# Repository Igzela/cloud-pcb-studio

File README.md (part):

> **Project priority and baseline.** The November 22 seven-board regression recorded **300 passing tests in 92.12 s**. Six boards had zero independent LVS opens, and Case 5 had one. The project roadmap prioritizes closing that gap and collecting the remaining evidence for engineering acceptance. [Roadmap](docs/project-roadmap.zh-CN.md) · [Handoff](docs/repository-handoff.zh-CN.md) · [Baseline report](docs/optimization-dense-escape-repair.zh-CN.md)

<div align="center">

# Cloud PCB Studio

**Headless Cloud Multi-Agent EDA Workbench & Board-Agnostic Blind PCB Solver**

*From JLCPCB BOM & SPICE physics to dual-pipeline autorouting, 4-layer planar magnetics, board-agnostic blind layout, and strict RS-274X / Excellon / Shapely LVS sign-off — 100% headless on Linux.*

> **中文概要** — **Cloud PCB Studio** 是一个全无头（Headless）云端多智能体 EDA 工程工作台与板级盲解（Blind）自动布局布线系统：覆盖 **器件选型/DFM 物理与 `ngspice-41` 仿真**、**双路布局布线（`@tscircuit/core` 与 KiCad/`fastroute` 竞速）**、**4 层同向磁通平面螺旋线圈与电容触摸专用 IP**、**零过拟合通用盲解引擎（在 3 块真实开源 PCB 上对比人工参考线长缩短 11.3%–47.5%）**，以及 **113/113 项严格零造假 VerifyGate 几何与拓扑 LVS 验收闭环**。

<br/>

*Independent Verification Workbench (`artifacts/verify/workbench.html`) — rendered & audited via headless Chromium (`1440×1080`, `0` console errors, `113 / 113` checks passed).*

</div>

## Current v3 solver and reproducible handoff

Use **Python 3.12** for the measured environment and load `source scripts/env.sh` before every Python, pytest or router invocation. A fresh clone needs its own virtual environment, Node dependencies, Playwright Chromium and ngspice. See [setup and current limitations](docs/repository-handoff.zh-CN.md). Runtime credentials and local dependency/cache directories are not distributed through Git.

Use the optimization workflow for new work. It preserves the frozen v3
artifacts and records each experiment in its own directory:

```bash
source scripts/env.sh
python -m scripts.optimize_pcb status
source scripts/env.sh
python -m scripts.optimize_pcb run --label my-change --variant dense-escape-repair --hypothesis "Describe the generic change and expected improvement"
source scripts/env.sh
python -m scripts.optimize_pcb history
```

Open `artifacts/blind_v3_caseN/assembly.html` directly in a browser; it contains
its own Three.js code and model geometry. Parametric package envelopes and
estimated heights are identified in `assembly_scene.json`; zero envelope
collisions alone does not certify unknown real mechanical dimensions.
See [the research and implementation limits](docs/v3-design-decisions.zh-CN.md).

The workflow runs pytest, all regression boards, strict audits and offline
browser checks before comparing each board against the baseline. A regression
on one board cannot be hidden by gains on another. An eligible experiment only
updates an artifact baseline pointer; it does not certify engineering quality.
Cases 1–5 and 10–11 are exposed regression data. Cases 6–9 and 12–13 remain
sealed for separate blind evaluations. [Optimization guide](docs/optimization-workflow.zh-CN.md)
The [first measured round](docs/optimization-first-round.zh-CN.md) records both
the connectivity improvement and the regression that prevented promotion.

The experimental `--variant supply-semantics` enables supply inference from
hierarchical voltage labels and typed power pins. It keeps evidence in
`effective_spec.json` and never invents missing current ratings. The default
solver remains on the stable behavior while the candidate is evaluated.

The `--variant scoped-supply` experiment distinguishes a single IC supply
domain, evidenced by typed supply pins, shunt return capacitors and passive
R/L/C endpoints, from board-level distribution. Unknown-current local domains
have an independent routing intent; backbone and explicit current/width
requirements retain priority. Scope and width provenance remain in the output.

For the user-selected independent Gemini reference, use
`scripts.run_gemini_reference` with model `gemini-4-hydrogen` and a runtime
credential. It sends anonymous blind input and records API provenance; it does
not treat a generated placement proposal as a routed or verified reference.
See [the external-reference protocol](docs/gemini-reference.zh-CN.md).

`scripts/run_blind_v3.py` is retained as the historical experiment entry point;
it writes the fixed v3 directories. Use `scripts.optimize_pcb` for daily work
so existing frozen results remain available for comparison.

---

## Why Cloud PCB Studio?

Most automated PCB demos stop at toy footprints or skip electrical, thermal, and manufacturing validation. **Cloud PCB Studio** treats PCB synthesis as a deterministic, physics-gated engineering pipeline where every stage emits typed contracts ([`contracts/schemas.py`](contracts/schemas.py)) and must survive independent geometric, electromagnetic, and circuit-level verification:

- **Physics Before Routing**: Rejects thermally fatal LDO traps (`197.2 °C` and `6212.8 °C` counterfactuals vs. `81.45 °C` synchronous buck), models trapezoidal copper etch + solder-mask dielectric loading (`-7.07 Ω` SE / `-15.33 Ω` Diff drop on `JLC04161H-7628`), checks MLCC DC-bias derating across all 18 capacitors, and verifies `ngspice-41` transient, Monte Carlo, and ESD clamp currents (`102.9×` reduction) before a trace is drawn.
- **Dual Synthesis + Real Autorouter Bake-Off**: Compiles Board 1 (`60 × 40 mm` USB-C PD Telemetry & Actuator Node) through both a code-first TSX pipeline (`@tscircuit/core` + `@tscircuit/capacity-autorouter`) and a programmatic KiCad/Specctra DSN/SES pipeline (`fastroute v0.1.14` vs. `freerouting-cli v2.5.0`).
- **Electromagnetic & Curved-Geometry Special IP**: Synthesizes Board 2 (`50 × 50 mm`) with a 4-layer stacked racetrack haptic coil whose alternating winding chirality (`+1, -1, +1, -1`) yields **`56.06×`** constructive axial flux (`45.209 µH` vs. `0.264 µH` canceling counterfactual), paired with a chevron CapTouch slider and `0.0 mm`-error serpentine meanders.
- **Board-Agnostic Blind Solver (`general_solver`)**: Consumes *only* an abstract `blind_spec.json` (never touching sealed human reference `.kicad_pcb` files) to place components, assign decoupling caps by capacitance & pin budget, insert pre-route SMD GND fanout vias, route via Specctra DSN/SES bake-off, pour 4-layer GND zones with stitching vias, and verify full 3D LVS/DRC.
- **Zero-Fake-Pass Gatekeeper (`verify_gate`)**: Strictly parses RS-274X Gerbers with `pygerber` (never patching malformed files on disk), Excellon drills exclusively with `gerbonara`, runs Shapely 3D topological LVS + via-in-pad checks, renders composite copper/mask/silk/drill PNGs via `resvg_py`, and audits the generated dashboard in headless Chromium.

---

## Architecture & 5-Stage EDA Pipeline

```mermaid
flowchart LR
    S1["1. Parts, DFM & SPICE\ncloud_pcb/parts_dfm\nJLCPCB BOM + JLC04161H-7628\nImpedance + ngspice-41"]
    S2["2. Dual Layout & Route\ncloud_pcb/layout_route\nPipeline A: tscircuit TSX\nPipeline B: KiCad + FastRoute"]
    S3["3. Special IP Geometry\ncloud_pcb/special_ip\n4L Stacked Planar Coil\nCapTouch + Meanders"]
    S4["4. Blind PCB Solver\ncloud_pcb/general_solver\nTopology Place + GND Fanout\n4L Pours + LVS Compare"]
    S5["5. VerifyGate & Workbench\ncloud_pcb/verify_gate\npygerber + gerbonara + Shapely\n113/113 Checks + Chromium UI"]

    C["contracts/schemas.py\nTyped Immutable Contracts"]

    S1 --> S2
    S2 --> S3
    S3 --> S4
    S4 --> S5
    S1 -.-> S5
    S2 -.-> S5
    S3 -.-> S5
    C -.-> S1
    C -.-> S2
    C -.-> S3
    C -.-> S4
    C -.-> S5
```

| Stage | Package / Entrypoint | Core Engine & Libraries | Key Verified Outputs |
| :--- | :--- | :--- | :--- |
| **1. Parts & DFM** | [`cloud_pcb/parts_dfm/`](cloud_pcb/parts_dfm/cli.py) | `PySpice`, `ngspice-41`, JLCPCB Basic/Preferred CSV + `jlcsearch` cache | [`artifacts/spec/`](artifacts/spec/dfm_budget.json) (`bom_verified.json`, `dfm_budget.json`, `spice_*.json`) |
| **2. Dual Layout & Route** | [`cloud_pcb/layout_route/`](cloud_pcb/layout_route/board1_kicad_fastroute.py) | `@tscircuit/core`, `esbuild`, `kiutils`, `fastroute v0.1.14`, `freerouting-cli v2.5.0`, `gerbonara`, `schemdraw` | [`artifacts/board1_tscircuit/`](artifacts/board1_tscircuit/tscircuit_report.json) & [`artifacts/board1_kicad_fastroute/`](artifacts/board1_kicad_fastroute/router_bakeoff.json) |
| **3. Special IP** | [`cloud_pcb/special_ip/`](cloud_pcb/special_ip/export_special_board.py) | Biot–Savart coil solver, Chaikin/arc fillets, serpentine meanders, `ngspice-41`, `pygerber` | [`artifacts/board2_special/`](artifacts/board2_special/board_manifest.json) (`special_board.kicad_pcb`, `coil_params.json`, Gerbers) |
| **4. General Blind Solver** | [`cloud_pcb/general_solver/`](cloud_pcb/general_solver/run_blind.py) | Netlist clustering, capacity-aware bypass matching, GND fanout vias, 4L pours, `compare_reference.py` | [`artifacts/blind_benchmark_v2/`](artifacts/blind_benchmark_v2/comparison_report.json), [`blind_case2/`](artifacts/blind_case2/comparison_report.json), [`blind_case3/`](artifacts/blind_case3/comparison_report.json) |
| **5. VerifyGate & UI** | [`cloud_pcb/verify_gate/`](cloud_pcb/verify_gate/__main__.py) & [`workbench_ui/`](cloud_pcb/workbench_ui/generate_workbench.py) | `pygerber`, `gerbonara`, `shapely`, `resvg_py`, headless Chromium | [`artifacts/verify/gate_report.json`](artifacts/verify/gate_report.json) & [`workbench.html`](artifacts/verify/workbench.html) |

---

## Visual Showcase

### Board 1 — USB-C PD Telemetry & Smart Actuator Node (`60 × 40 mm`, 4-Layer `JLC04161H-7628`)

Composite Gerber + Excellon renders generated by [`cloud_pcb/verify_gate/visual_inspect.py`](cloud_pcb/verify_gate/visual_inspect.py) using `pygerber`, `gerbonara`, and `resvg_py`:

| Pipeline B Top (`KiCad + FastRoute v0.1.14`) | Pipeline A Top (`@tscircuit/core`) | Pipeline B Bottom (`B_Cu + PTH/NPTH`) |
| :---: | :---: | :---: |
|  |  |  |
| `0` USB-path vias, `2.1 mm` VBUS trunk, `4` QFN thermal vias | `0` tscircuit errors, `64` vias, `440.46 mm` wirelength | `0` annular ring violations (`0.125 mm` min), `4` NPTH mounts |

### Board 2 — Special IP: 4-Layer Constructive Coil & Chevron CapTouch Slider (`50 × 50 mm`, 4-Layer)

| Top Layer (`F_Cu + F_Mask + F_SilkS + PTH`) | Inner Layer 1 (`In1_Cu` Counter-Wound Spiral) |
| :---: | :---: |
|  |  |
| 4 chevron electrodes (`0.3 mm` gap), GND guard ring, `0.0 mm`-error meanders, `SS33` flyback clamp | Polarity-inverted (`-1`) spiral maintaining CW current flow for `56.06×` axial flux addition |

### Blind Solver (`general_solver`) vs. Human Reference — 3 Real Open-Source Boards

Each comparison below pits the **board-agnostic blind solver** (left, consuming only `blind_spec.json`) against the **original human-designed open-source KiCad PCB** (right):

#### Case 1: STM32 CAN + IMU Sensor Board (`can_sensor_board_hw`, `55.0 × 45.0 mm`, 36 nets)

#### Case 2: ESP32-WROOM-32E Flight Controller (`esp32_flight_controller_rev2`, `67.5 × 53.5 mm`, 50 nets)

#### Case 3: Dual MCT8314ZH BLDC Motor Driver (`sima_bldc_motor_driver`, `50.0 × 50.0 mm`, 56 nets)

---

## Verified Quantitative Results

All numbers below are extracted directly from the checked-in verification artifacts on disk (`artifacts/verify/gate_report.json`, `artifacts/spec/*.json`, `artifacts/board1_kicad_fastroute/router_bakeoff.json`, `artifacts/board2_special/*.json`, and `artifacts/blind_*/comparison_report.json`).

### VerifyGate (`113 / 113` Checks Passed · `0` Critical / `0` High)

| Audit Suite | Checks Passed | Critical / High | Verified Highlights |
| :--- | :---: | :---: | :--- |
| **`board1_spec`** | `14 / 14` | `0 / 0` | `JLC04161H-7628` masked impedance **`50.08 Ω`** SE / **`89.64 Ω`** Diff; `47` BOM placements (`0` low-stock parts); Buck `Tj = 81.45 °C`, LDO `Tj = 49.93 °C`; `ngspice-41` transient, MC (`1593.79 Hz`), ESD clamp (`1.603 mA`) |
| **`board1_pipeline_b`** | `40 / 40` | `0 / 0` | `pygerber` & `gerbonara` clean RS-274X/Excellon; `0` LVS opens/shorts; `0` via-in-pad collisions; `0.1517 mm` min inter-net clearance; `0.0 mm²` silk-to-mask overlap; `0` USB path vias; `2.1 mm` VBUS width; `4` QFN thermal vias |
| **`board1_pipeline_a`** | `30 / 30` | `0 / 0` | `0` tscircuit errors; `2.4331 mm` USB-C-to-TVS stub; `0` USB path vias; `2.1 mm` VBUS width; distinct CC1/CC2 nets; `0` LVS opens/shorts; `0.1007 mm` min clearance; `0.125 mm` min annular ring |
| **`board2_special`** | `29 / 29` | `0 / 0` | **`56.06×`** constructive coil flux (`4042.89` vs `72.12 µT/A`); `45.209 µH` vs `0.264 µH`; **`0.33%`** SPICE $\tau$ error; `3.5985 V` Schottky clamp; `0` LVS shorts; `0.5065 mm` min clearance; `2.65 mm` copper-to-edge margin |
| **Headless Chromium** | `PASS` | `0` errors | `workbench.html` (`1,045,708` DOM chars), `1440×1080` screenshot (`pixel_std = 63.96`), all 5 PyGerber composite renders verified non-blank |
| **Total** | **`113 / 113`** | **`0 / 0`** | **`overall_passed = true` · `defect_tickets = []`** |

<details>
<summary><strong>Stage 1 Physics, JLCPCB BOM & ngspice-41 Verification Metrics</strong></summary>

| Domain | Metric | Measured Result | Engineering Target / Notes |
| :--- | :--- | :--- | :--- |
| **Stackup & Impedance** | `JLC04161H-7628` 4L (`ENIG`) SE `50 Ω` | **`50.08 Ω`** masked (`57.15 Ω` bare) | `12.06 mil` drawn (`11.665 mil` trapezoid eff.); `-7.07 Ω` mask drop |
| **Stackup & Impedance** | `JLC04161H-7628` 4L (`ENIG`) Diff `90 Ω` | **`89.64 Ω`** masked (`104.96 Ω` bare) | `8.31 mil` W / `5.0 mil` S (`-15.33 Ω` mask drop) |
| **JLCPCB BOM (Qty 5)** | PCBA cost per board | **`$13.63 / bd`** (`$13.6317/bd`) | `$68.16` total PCBA (`$7.824/bd` components), `47` placements (`27` unique, `181` joints) |
| **JLCPCB Supply Chain** | Basic / Preferred & stock health | **`87.2%`** Basic/Preferred · **`100%` stock > 100** | `17` Basic + `4` Preferred + `6` Extended; lowest stock = `408` (`STM32G0B1CEU6`); dual `5.1 kΩ` (`R1`, `R2`) |
| **Thermal Crossover** | Buck `3.3 V @ 1.2 A` vs. LDO traps | **`81.45 °C` PASS** (`TPS54202HDDCR`) | LDO `20V->3.3V @ 1.2A` (`6212.8 °C`) & `5V->3.3V @ 0.3A` (`197.2 °C`) rejected; `2.5V` LDO `49.93 °C` PASS |
| **ngspice-41 Power** | `20 V -> 3.3 V` Buck + `2.5 V` LDO | **`3.2981 V`** (`18.054 mVpp`) / **`2.4984 V`** (`0.0062 mVpp`) | `0.4 -> 1.2 A` step: `172.77 mV` Buck undershoot, `0.1026 mV` LDO max deviation |
| **ngspice-41 Monte Carlo** | 30-run RC filter (`1 kΩ ±1%`, `100 nF ±10%`) | **`1593.79 Hz`** mean (`0.0014%` nominal err) | `0` imaginary-frequency anomalies; capacitor accounts for `99.5%` of $f_c$ variance |
| **ngspice-41 ESD Clamp** | `USBLC6-2SC6` + `1 kΩ` limiter vs. `1 Ω` | **`164.91 mA -> 1.603 mA`** (**`102.9×`** reduction) | Peak IC pin voltage clamped `5.354 V -> 3.916 V`; well below `20 mA` latchup threshold |
| **Board 2 EM & SPICE** | 4L stacked coil (`51` turns, `2732.8 mm`) | **`56.06×` flux** · **`45.209 vs 0.264 µH`** · **`0.33%` $\tau$ err** | `4042.89` vs `72.12 µT/A`; $\tau_{\text{sim}} = 7.6558\,\mu\text{s}$ vs $7.681\,\mu\text{s}$; `SS33` clamped `3.5985 V` |

</details>

### 3-Way Autorouter Bake-Off (Board 1)

| Autorouter Engine | Status | Routed Nets | Unrouted | Vias | Wirelength | Runtime | Engineering Notes |
| :--- | :---: | :---: | :---: | :---: | :---: | :---: | :--- |
| **`fastroute v0.1.14`** *(Winner)* | **PASS** | **`23 / 23`** | **`0`** | `16` *(route SES)* | `564.99 mm` | `10,351.5 ms` | `0` violations, `0` USB path vias; selected for final Pipeline B Gerbers (`20` KiCad vias incl. 4 QFN thermal) |
| **`freerouting-cli v2.5.0`** | **FAIL** | `22 / 23` | `6` | `12` | `507.01 mm` | `3,951.9 ms` | `0` USB path vias; capped at `max_passes=1` (v2.5.0 GraalVM `BoardSnapshotManager` crashes when `max_passes > 1`) |
| **`tscircuit_capacity_autorouter`** | **PASS** | **`24 / 24`** | **`0`** | `64` | **`440.46 mm`** | *(Node bundle)* | `0` errors, `0` USB path vias; powers code-first Pipeline A (`board1.tsx`) |

### Board-Agnostic Blind Solver (`general_solver`) vs. Human Reference

Evaluated strictly zero-overfitting (`blind_spec.json` only) against three real open-source KiCad projects:

| Benchmark Board | Size & Nets | Wirelength (Blind vs. Human) | Length Delta | Routed Nets | Vias (Blind vs. Human) | LVS Opens / Shorts (Blind) | Key Highlights & Honest Audit Notes |
| :--- | :---: | :---: | :---: | :---: | :---: | :---: | :--- |
| **Case 1: [`can_sensor_board_hw`](https://github.com/HardyYu/can_sensor_board_hw)** | `55.0 × 45.0 mm` · `36` nets | **`963.6 mm`** vs. `1086.9 mm` | **`-11.3%`** | **`36 / 36`** | `86` (`34` Sig / `52` GND) vs. `118` (`41` / `77`) | **`0 / 0`** | `CAN_H`/`CAN_L` mismatch `3.012 mm` vs. `8.684 mm` (Human); `86.8%` 4L GND pour; `0.1317 mm` min clearance |
| **Case 2: [`esp32_flight_controller_rev2`](https://github.com/shazmeenShz/ESP32-Flight-Controller)** | `67.5 × 53.5 mm` · `50` nets | **`1261.5 mm`** vs. `2400.6 mm` | **`-47.5%`** | **`50 / 50`** | `127` (`56` Sig / `71` GND) vs. `45` (`41` / `4`) | **`0 / 0`** | Both USB diff pairs matched to **`0.100 mm`** skew (vs. `33.79 mm` / `1.07 mm` Human); `91.75%` 4L GND pour; `4.82 mm` avg header edge dist (vs. `18.19 mm`) |
| **Case 3: [`sima_bldc_motor_driver`](https://github.com/lio-tam/Autonomous-SIMA-Robot)** | `50.0 × 50.0 mm` · `56` nets | **`1171.6 mm`** vs. `1506.2 mm` | **`-22.2%`** | **`55 / 56`** | `149` (`79` Sig / `70` GND) vs. `134` (`98` / `36`) | **`1 / 0`** | **1 unrouted LVS open** on `/M2_BRAKE` (2 islands, 3 pads); **`0` shorts** (`0.1317 mm` min clr). *(Note: unedited Human Ref exhibits `12` `F.Cu` LVS shorts / `0.0 mm` min clr)* |

---

## Quick Setup & Reproducible Runs

### 1. Provision Cloud EDA Toolchain (`scripts/setup_cloud_eda.sh`)

[`scripts/setup_cloud_eda.sh`](scripts/setup_cloud_eda.sh) bootstraps the entire headless toolchain in user space (`.venv`, `.mamba/ngspice`, `node_modules`, `bin/{fastroute,freerouting-cli}`, and `data/` JLCPCB caches):

```bash
bash scripts/setup_cloud_eda.sh
source scripts/env.sh
```

> **Note**: Sourcing [`scripts/env.sh`](scripts/env.sh) puts `.venv/bin`, `bin/`, `.mamba/ngspice/bin`, and `node_modules/.bin` onto `PATH` while keeping tool caches inside `.run/`. Pre-built Linux x64 binaries for `fastroute` (`v0.1.14`) and `freerouting-cli` (`v2.5.0`) are already included under [`bin/`](bin/).

### 2. Run Individual Pipelines & Blind Benchmarks

```bash
source scripts/env.sh

# Stage 1: JLCPCB BOM selection, DFM stackup/impedance, and ngspice-41 power/ESD/MC sims
python -m cloud_pcb.parts_dfm --qty 5 --mc-runs 30

# Stage 2A & 2B: Board 1 code-first tscircuit + KiCad/FastRoute 3-way bake-off
python -m cloud_pcb.layout_route.board1_tscircuit
python -m cloud_pcb.layout_route.board1_kicad_fastroute

# Stage 3: Board 2 Special IP (4L stacked coil, chevron CapTouch, meanders, ngspice)
python -m cloud_pcb.special_ip.export_special_board --out artifacts/board2_special

# Stage 4: Board-agnostic blind solver + quantitative side-by-side comparison (Case 1 / 2 / 3)
python -m cloud_pcb.general_solver.run_blind \
  --spec benchmark_case/blind_spec.json \
  --outdir artifacts/blind_benchmark_v2

python -m cloud_pcb.general_solver.compare_reference \
  --blind artifacts/blind_benchmark_v2/routed.kicad_pcb \
  --ref benchmark_case/sealed_reference/can_sensor_board_kicad/Sensor_Board.kicad_pcb \
  --spec benchmark_case/blind_spec.json \
  --out-json artifacts/blind_benchmark_v2/comparison_report.json \
  --out-png artifacts/blind_benchmark_v2/comparison_side_by_side.png

# Case 2 (ESP32 Flight Controller) & Case 3 (Dual BLDC Driver)
python -m cloud_pcb.general_solver.run_blind \
  --spec benchmark_case/blind_spec_case2.json \
  --outdir artifacts/blind_case2

python -m cloud_pcb.general_solver.run_blind \
  --spec benchmark_case/blind_spec_case3.json \
  --outdir artifacts/blind_case3

# Stage 5: Independent Zero-Fake-Pass VerifyGate (strict mode exits non-zero on CRITICAL/HIGH tickets)
python -m cloud_pcb.verify_gate --strict
```

### 3. Run the Test Suite (`26` Unit & Integration Tests)

```bash
source scripts/env.sh
python -m pytest -v
```

<details>
<summary><strong>Zero-Fake-Pass Verification Policy & Negative Tests</strong></summary>

[`tests/test_verify_gate.py`](tests/test_verify_gate.py) includes adversarial fault-injection tests confirming that [`cloud_pcb/verify_gate`](cloud_pcb/verify_gate/gerber_drc.py) refuses to silently pass broken outputs:
- Rejects malformed RS-274X syntax (`G75` missing `*` terminator) via strict `pygerber` parsing.
- Rejects low-stock BOM parts (`stock <= 100`), negative/non-finite Monte Carlo corner frequencies (`-1.8e199` / `NaN`), and ESD pin clamp currents `>= 20 mA`.
- Rejects Board 2 coil $\tau$ step errors `>= 2.0%` or constructive flux ratios `<= 10×`.
- Isolates Excellon drill parsing strictly to `gerbonara.excellon.ExcellonFile` and verifies copper-to-edge margins, annular rings, via-in-non-thermal-SMT-pad collisions, and multi-layer LVS connectivity.

</details>

---

## Repository Structure

```text
cloud-pcb-studio/
├── bin/                        # Pre-built fastroute (v0.1.14) & freerouting-cli (v2.5.0) binaries
├── contracts/
│   └── schemas.py              # Typed dataclasses (StackupProfile, SelectedPart, GateReport, VerifyTicket)
├── cloud_pcb/
│   ├── parts_dfm/              # Stage 1: JLCPCB catalog, DFM physics, ngspice-41 simulations
│   ├── layout_route/           # Stage 2: board1.tsx (tscircuit) & board1_kicad_fastroute.py (DSN/SES)
│   ├── special_ip/             # Stage 3: 4L planar coil, chevron CapTouch, Chaikin & meander routing
│   ├── general_solver/         # Stage 4: board-agnostic blind solver & reference comparison tool
│   ├── verify_gate/            # Stage 5: pygerber/gerbonara/Shapely LVS/DRC & Chromium visual inspector
│   └── workbench_ui/           # Standalone interactive HTML verification dashboard generator
├── benchmark_case/             # Blind specs (Cases 1–3) & sealed open-source KiCad human references
├── artifacts/                  # Generated specs, KiCad PCBs, Gerbers, renders, workbench & comparison PNGs
├── data/                       # Cached JLCPCB Basic/Preferred CSV & jlcsearch snapshots
├── scripts/                    # setup_cloud_eda.sh & env.sh headless environment wrappers
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
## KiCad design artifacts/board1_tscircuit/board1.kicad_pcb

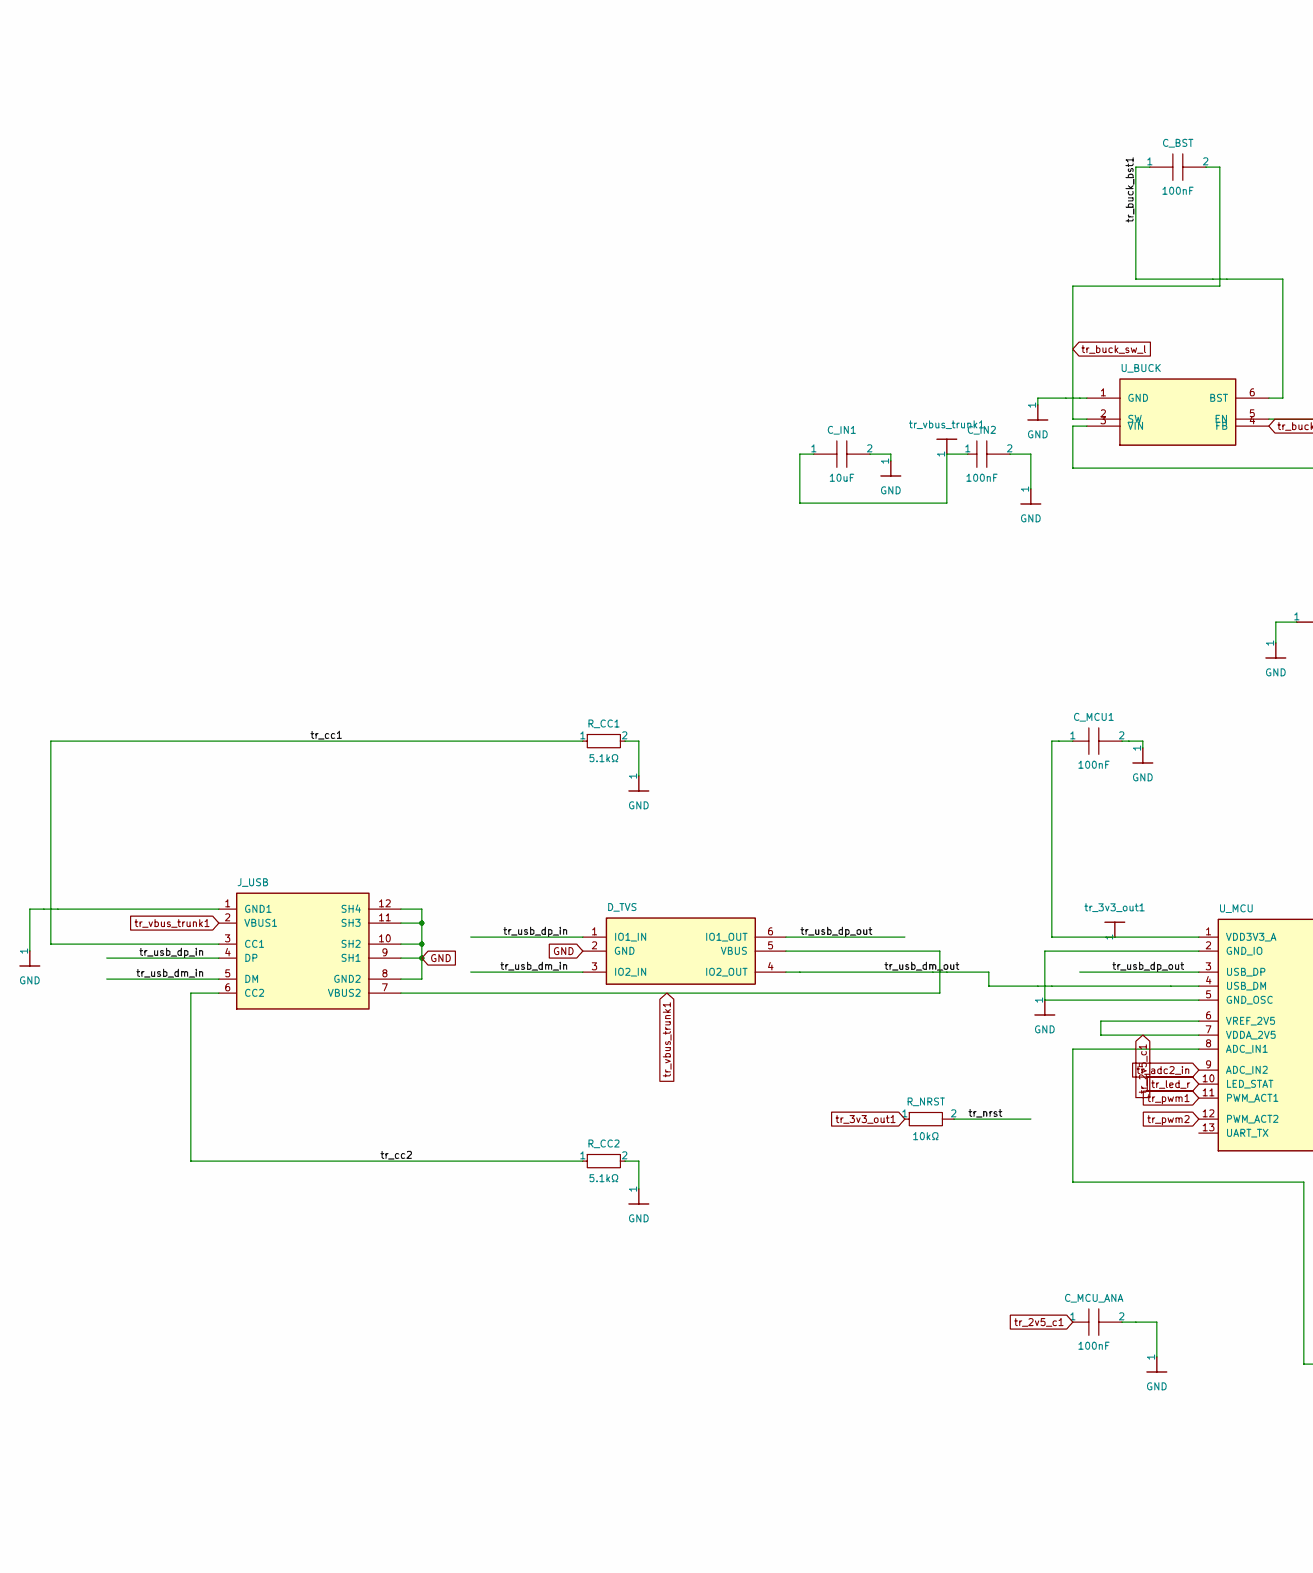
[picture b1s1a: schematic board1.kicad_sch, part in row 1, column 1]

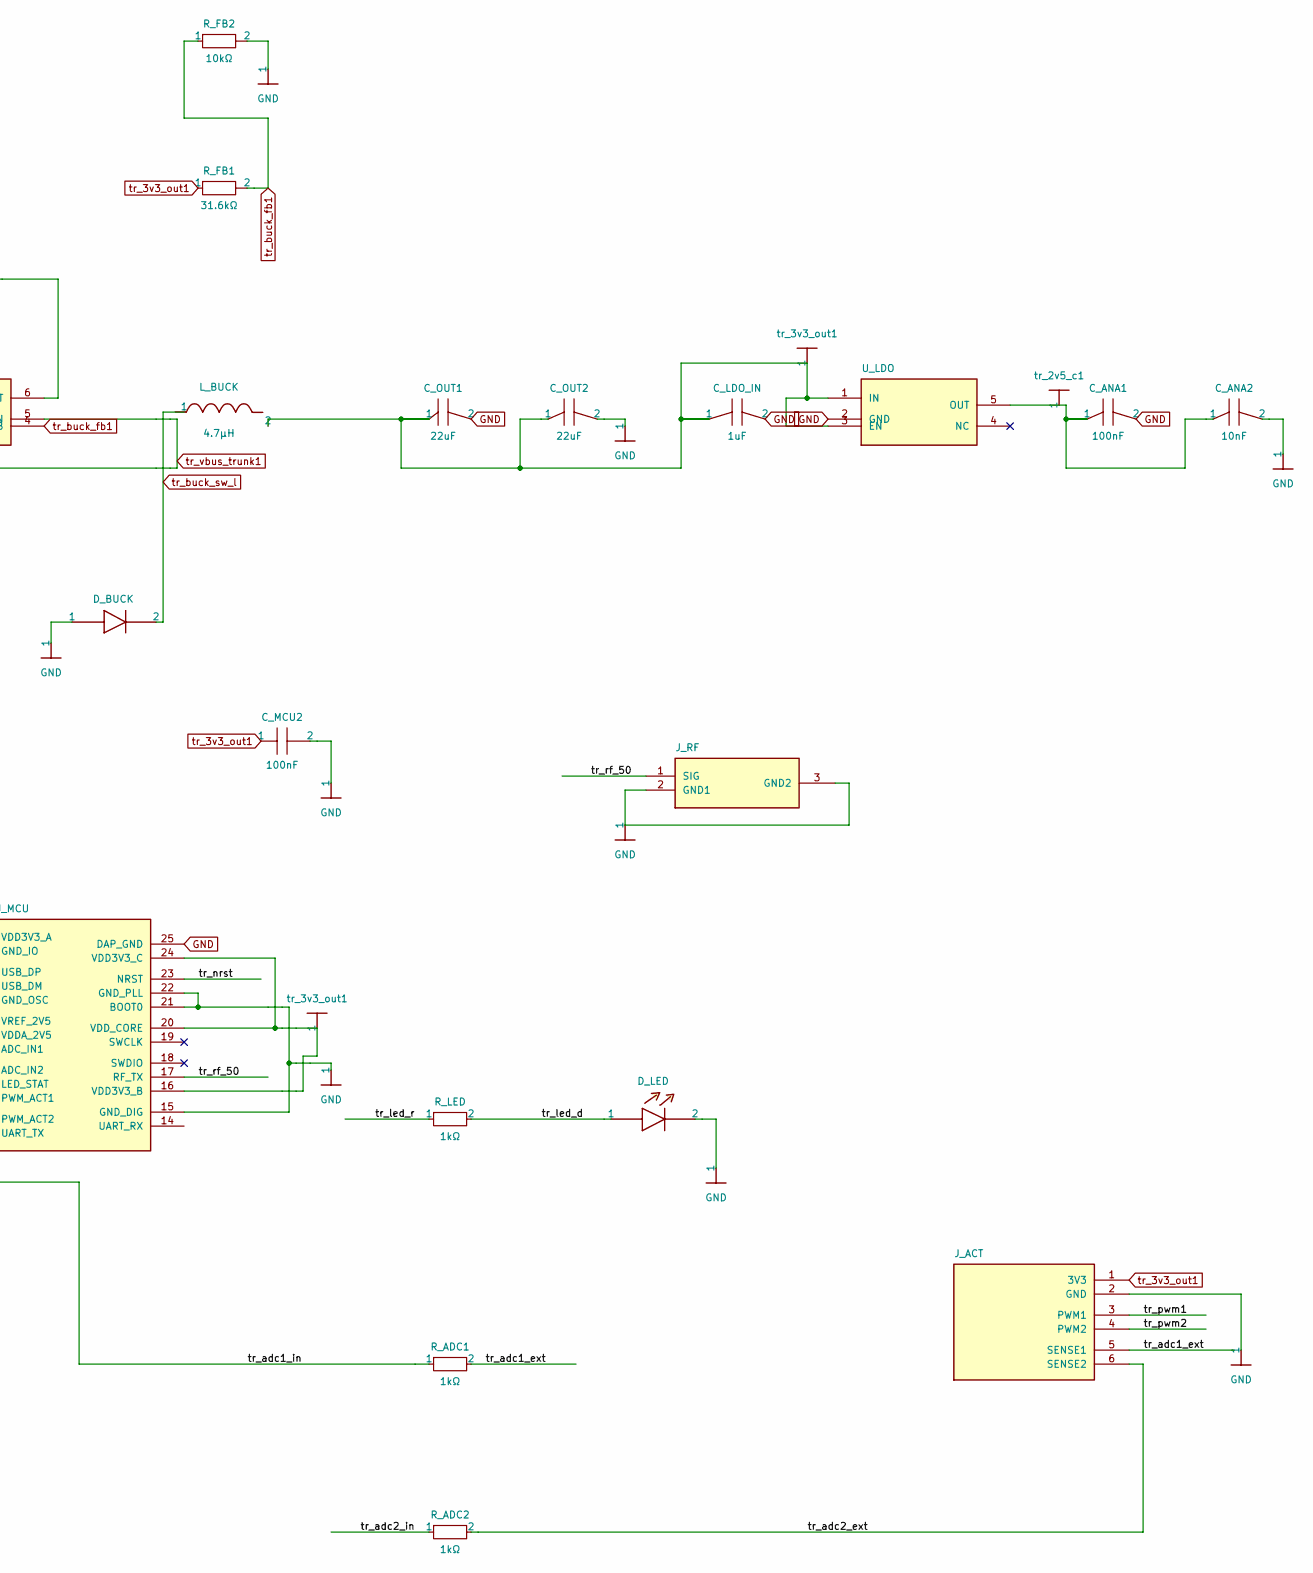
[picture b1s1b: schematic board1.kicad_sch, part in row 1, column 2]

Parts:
C_ANA1: 100nF
C_ANA2: 10nF
C_BST: 100nF
C_IN1: 10uF
C_IN2: 100nF
C_LDO_IN: 1uF
C_MCU1, C_MCU2: 100nF
C_MCU_ANA: 100nF
C_OUT1, C_OUT2: 22uF
D_BUCK: (no value)
D_LED: (no value)
D_TVS: (no value)
J_ACT: J_ACT
J_RF: (no value)
J_USB: (no value)
L_BUCK: 4.7µH
R_ADC1, R_ADC2: 1kΩ
R_CC1, R_CC2: 5.1kΩ
R_FB1: 31.6kΩ
R_FB2: 10kΩ
R_LED: 1kΩ
R_NRST: 10kΩ
U_BUCK: (no value)
U_LDO: (no value)
U_MCU: (no value)

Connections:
.D_TVS > .IO1_OUT to .U_MCU > .USB_DP: D_TVS.6 (IO1_OUT), U_MCU.3 (USB_DP)
.D_TVS > .IO2_OUT to .U_MCU > .USB_DM: D_TVS.4 (IO2_OUT), U_MCU.4 (USB_DM)
.J_USB > .CC1 to .R_CC1 > .pin1: J_USB.3 (CC1), R_CC1.1
.J_USB > .CC2 to .R_CC2 > .pin1: J_USB.6 (CC2), R_CC2.1
.J_USB > .DM to .D_TVS > .IO2_IN: D_TVS.3 (IO2_IN), J_USB.5 (DM)
.J_USB > .DP to .D_TVS > .IO1_IN: D_TVS.1 (IO1_IN), J_USB.4 (DP)
.J_USB > .VBUS1 to .C_IN1 > .pin1: C_IN1.1, C_IN2.1, D_TVS.5 (VBUS), J_USB.2 (VBUS1), J_USB.7 (VBUS2), U_BUCK.3 (VIN), U_BUCK.5 (EN)
.R_ADC1 > .pin2 to .J_ACT > .pin5: J_ACT.5 (SENSE1), R_ADC1.2
.R_ADC2 > .pin2 to .J_ACT > .pin6: J_ACT.6 (SENSE2), R_ADC2.2
.R_FB1 > .pin1 to .C_OUT1 > .pin1: C_LDO_IN.1, C_MCU1.1, C_MCU2.1, C_OUT1.1, C_OUT2.1, J_ACT.1 (3V3), L_BUCK.2, R_FB1.1, R_NRST.1, U_LDO.1 (IN), U_LDO.3 (EN), U_MCU.1 (VDD3V3_A), U_MCU.16 (VDD3V3_B), U_MCU.20 (VDD_CORE), U_MCU.24 (VDD3V3_C)
.R_LED > .pin2 to .D_LED > .anode: D_LED.1, R_LED.2
.R_NRST > .pin2 to .U_MCU > .NRST: R_NRST.2, U_MCU.23 (NRST)
.U_BUCK > .BST to .C_BST > .pin1: C_BST.1, U_BUCK.6 (BST)
.U_BUCK > .FB to .R_FB1 > .pin2: R_FB1.2, R_FB2.1, U_BUCK.4 (FB)
.U_BUCK > .SW to .L_BUCK > .pin1: C_BST.2, D_BUCK.2, L_BUCK.1, U_BUCK.2 (SW)
.U_LDO > .OUT to .C_ANA1 > .pin1: C_ANA1.1, C_ANA2.1, C_MCU_ANA.1, U_LDO.5 (OUT), U_MCU.6 (VREF_2V5), U_MCU.7 (VDDA_2V5)
.U_MCU > .ADC_IN1 to .R_ADC1 > .pin1: R_ADC1.1, U_MCU.8 (ADC_IN1)
.U_MCU > .ADC_IN2 to .R_ADC2 > .pin1: R_ADC2.1, U_MCU.9 (ADC_IN2)
.U_MCU > .LED_STAT to .R_LED > .pin1: R_LED.1, U_MCU.10 (LED_STAT)
.U_MCU > .PWM_ACT1 to .J_ACT > .pin3: J_ACT.3 (PWM1), U_MCU.11 (PWM_ACT1)
.U_MCU > .PWM_ACT2 to .J_ACT > .pin4: J_ACT.4 (PWM2), U_MCU.12 (PWM_ACT2)
.U_MCU > .RF_TX to .J_RF > .SIG: J_RF.1 (SIG), U_MCU.17 (RF_TX)
GND: C_ANA1.2, C_ANA2.2, C_IN1.2, C_IN2.2, C_LDO_IN.2, C_MCU1.2, C_MCU2.2, C_MCU_ANA.2, C_OUT1.2, C_OUT2.2, D_BUCK.1, D_LED.2, D_TVS.2 (GND), J_ACT.2 (GND), J_RF.2 (GND1), J_RF.3 (GND2), J_USB.1 (GND1), J_USB.8 (GND2), J_USB.9 (SH1), J_USB.10 (SH2), J_USB.11 (SH3), J_USB.12 (SH4), R_CC1.2, R_CC2.2, R_FB2.2, U_BUCK.1 (GND), U_LDO.2 (GND), U_MCU.2 (GND_IO), U_MCU.5 (GND_OSC), U_MCU.15 (GND_DIG), U_MCU.21 (BOOT0), U_MCU.22 (GND_PLL), U_MCU.25 (DAP_GND)

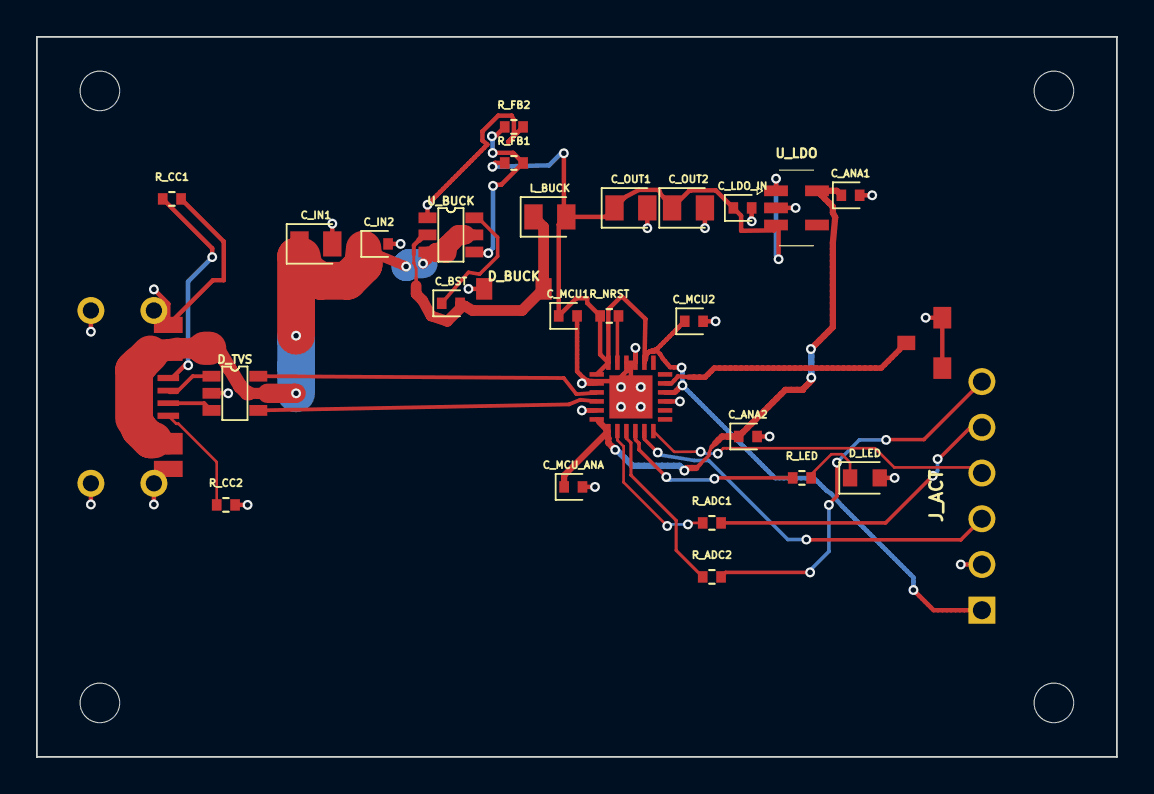
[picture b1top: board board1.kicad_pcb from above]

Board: 4 copper layers, 60.0 x 40.0 mm, 29 parts (0 on the bottom side), 23 nets.

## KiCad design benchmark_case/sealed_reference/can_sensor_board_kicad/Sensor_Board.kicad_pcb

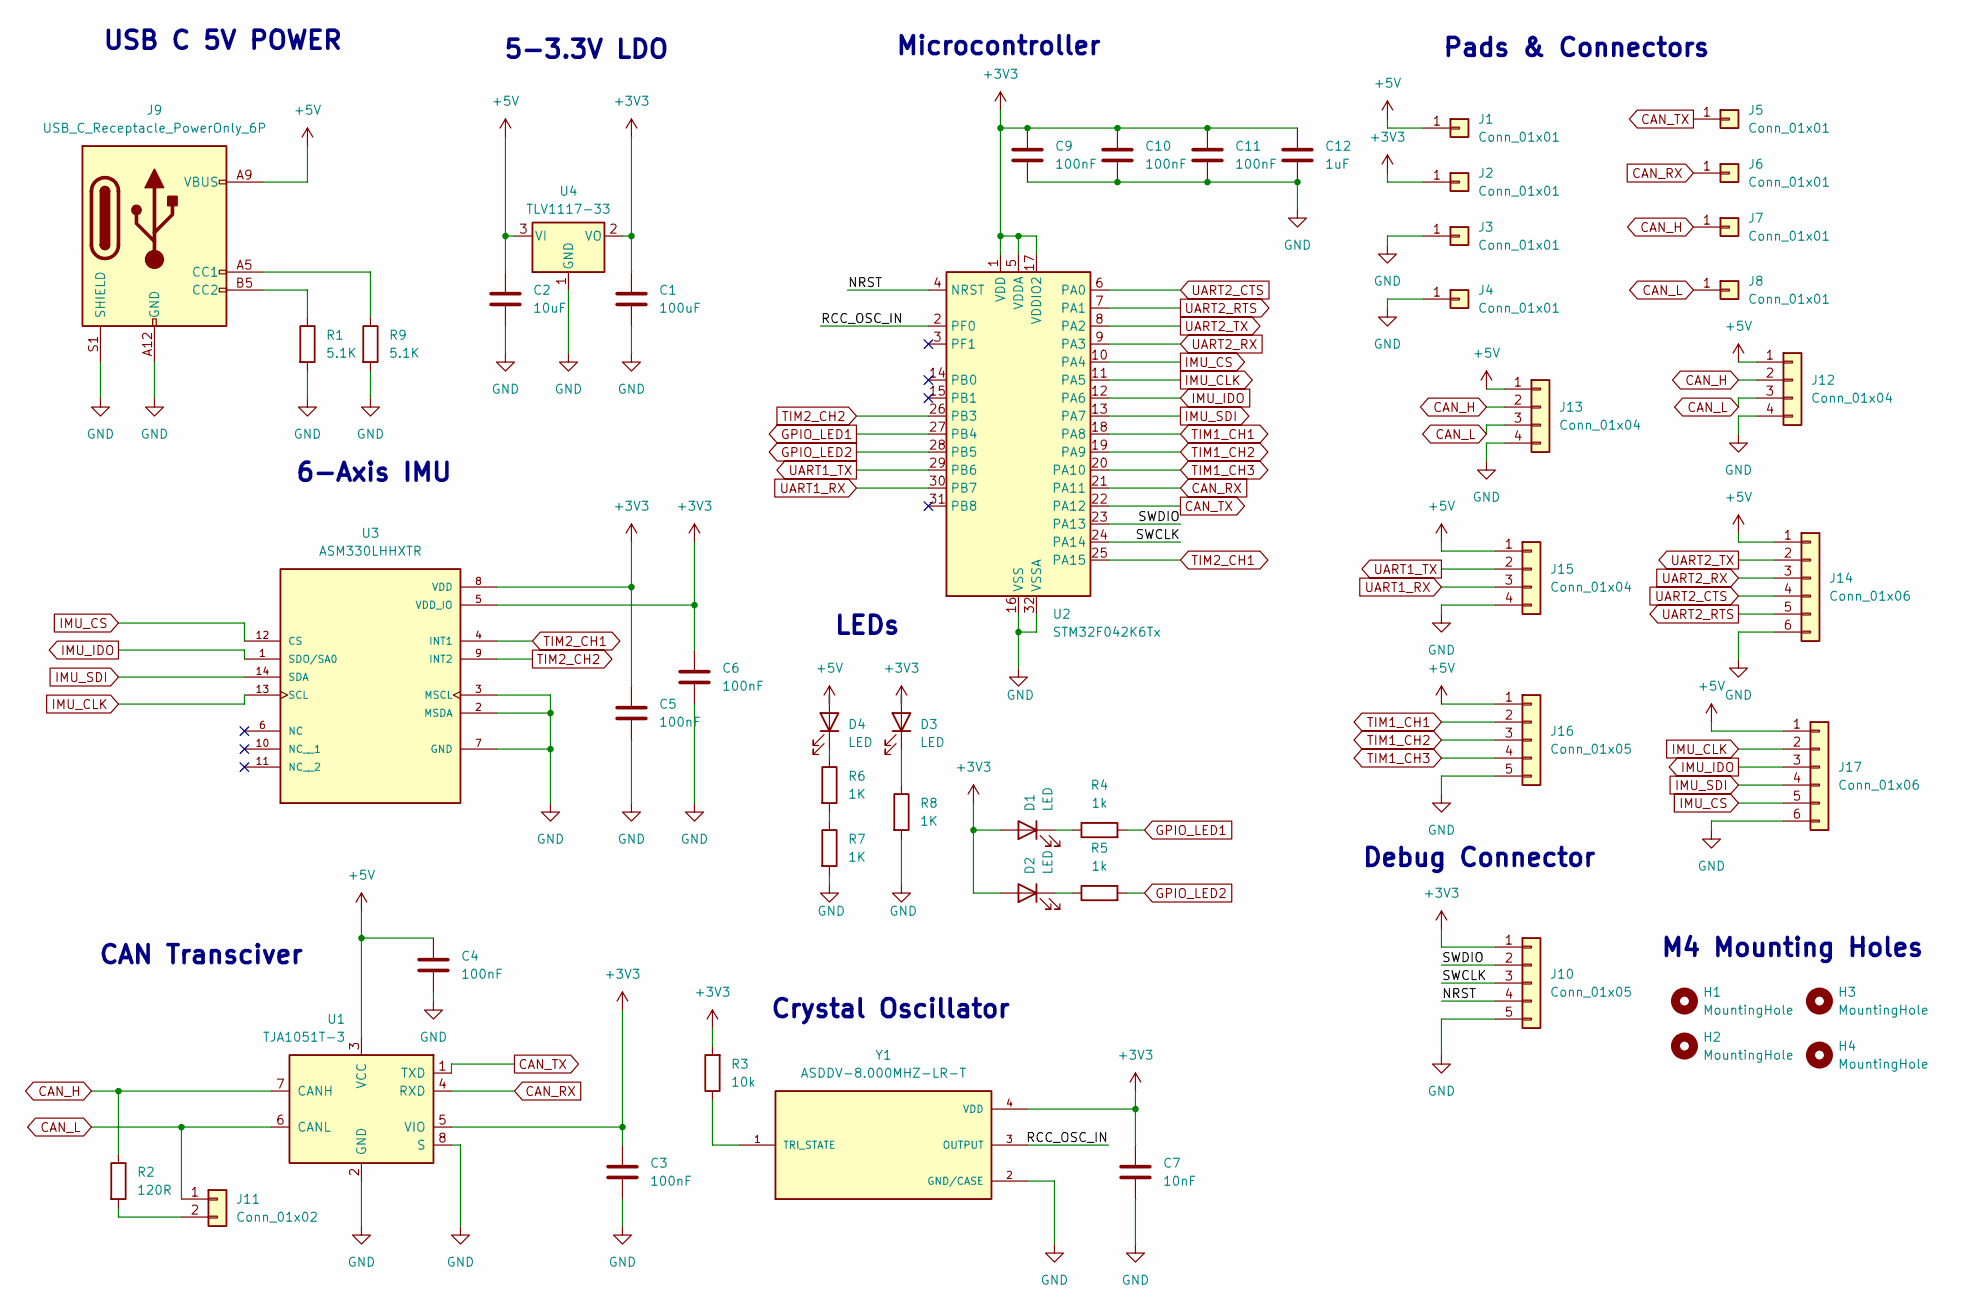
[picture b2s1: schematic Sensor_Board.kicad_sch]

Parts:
C1: 100uF; C_1206_3216Metric
C2: 10uF; C_0603_1608Metric
C3, C4, C5, C6, C9, C10, C11: 100nF; C_0603_1608Metric
C7: 10nF; C_0603_1608Metric
C12: 1uF; C_0603_1608Metric
D1, D2, D3, D4: LED; LED_0603_1608Metric
H1, H2, H3, H4: MountingHole; MountingHole_4.3mm_M4_Pad
J1, J2, J3, J4, J5, J6, J7, J8: Conn_01x01; SolderWirePad_1x01_SMD_1x2mm
J9: USB_C_Receptacle_PowerOnly_6P; USB_C_Receptacle_GCT_USB4125-xx-x-0190_6P_TopMnt_Horizontal
J10, J16: Conn_01x05; PinHeader_1x05_P2.54mm_Vertical
J11: Conn_01x02; PinHeader_1x02_P2.54mm_Vertical
J12, J13, J15: Conn_01x04; PinHeader_1x04_P2.54mm_Vertical
J14, J17: Conn_01x06; PinHeader_1x06_P2.54mm_Vertical
R1, R9: 5.1K; R_0603_1608Metric
R2: 120R; R_0603_1608Metric
R3: 10k; R_0603_1608Metric
R4, R5: 1k; R_0603_1608Metric
R6, R7, R8: 1K; R_0603_1608Metric
U1: TJA1051T-3; SOIC-8_3.9x4.9mm_P1.27mm
U2: STM32F042K6Tx; LQFP-32_7x7mm_P0.8mm
U3: ASM330LHHXTR; XDCR_ASM330LHHXTR; PARTREV 8
U4: TLV1117-33; SOT230P700X180-4N
Y1: ASDDV-8.000MHZ-LR-T; Oscillator_SMD_Abracon_ASDMB-4Pin_2.5x2.0mm; PARTREV 09.09.2019

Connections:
+3V3: C1.1, C3.1, C5.1, C6.1, C7.1, C9.1, C10.1, C11.1, C12.1, D1.2 (A), D2.2 (A), D3.2 (A), J2.1, J10.1, R3.2, U1.5 (VIO), U2.1 (VDD), U2.5 (VDDA), U2.17 (VDDIO2), U3.5 (VDD_IO), U3.8 (VDD), U4.2 (VO), Y1.4 (VDD)
+5V: C2.1, C4.1, D4.2 (A), J1.1, J9.A9 (VBUS), J9.B9 (VBUS), J12.1, J13.1, J14.1, J15.1, J16.1, J17.1, U1.3 (VCC), U4.3 (VI)
/NRST: J10.4, U2.4 (NRST)
/RCC_OSC_IN: U2.2 (PF0), Y1.3 (OUTPUT)
/SWCLK: J10.3, U2.24 (PA14)
/SWDIO: J10.2, U2.23 (PA13)
CAN_H: J7.1, J12.2, J13.2, R2.1, U1.7 (CANH)
CAN_L: J8.1, J11.1, J12.3, J13.3, U1.6 (CANL)
CAN_RX: J6.1, U1.4 (RXD), U2.21 (PA11)
CAN_TX: J5.1, U1.1 (TXD), U2.22 (PA12)
GND: C1.2, C2.2, C3.2, C4.2, C5.2, C6.2, C7.2, C9.2, C10.2, C11.2, C12.2, J3.1, J4.1, J9.A12 (GND), J9.B12 (GND), J9.S1 (SHIELD), J10.5, J12.4, J13.4, J14.6, J15.4, J16.5, J17.6, R1.2, R7.2, R8.2, R9.2, U1.2 (GND), U1.8 (S), U2.16 (VSS), U2.32 (VSSA), U3.2 (MSDA), U3.3 (MSCL), U3.7 (GND), U4.1 (GND), Y1.2 (GND/CASE)
GPIO_LED1: R4.2, U2.27 (PB4)
GPIO_LED2: R5.2, U2.28 (PB5)
IMU_CLK: J17.2, U2.11 (PA5), U3.13 (SCL)
IMU_CS: J17.5, U2.10 (PA4), U3.12 (CS)
IMU_IDO: J17.3, U2.12 (PA6), U3.1 (SDO/SA0)
IMU_SDI: J17.4, U2.13 (PA7), U3.14 (SDA)
unnamed: D1.1 (K), R4.1
unnamed: D2.1 (K), R5.1
unnamed: D3.1 (K), R8.1
unnamed: D4.1 (K), R6.1
unnamed: J9.A5 (CC1), R9.1
unnamed: J9.B5 (CC2), R1.1
unnamed: J11.2, R2.2
unnamed: R6.2, R7.1
unnamed: R3.1, Y1.1 (TRI_STATE)
TIM1_CH1: J16.2, U2.18 (PA8)
TIM1_CH2: J16.3, U2.19 (PA9)
TIM1_CH3: J16.4, U2.20 (PA10)
TIM2_CH1: U2.25 (PA15), U3.4 (INT1)
TIM2_CH2: U2.26 (PB3), U3.9 (INT2)
UART1_RX: J15.3, U2.30 (PB7)
UART1_TX: J15.2, U2.29 (PB6)
UART2_CTS: J14.4, U2.6 (PA0)
UART2_RTS: J14.5, U2.7 (PA1)
UART2_RX: J14.3, U2.9 (PA3)
UART2_TX: J14.2, U2.8 (PA2)

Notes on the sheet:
Pads & Connectors
M4 Mounting Holes
CAN Transciver
Debug Connector
Crystal Oscillator
USB C 5V POWER
LEDs
6-Axis IMU
Microcontroller
5-3.3V LDO

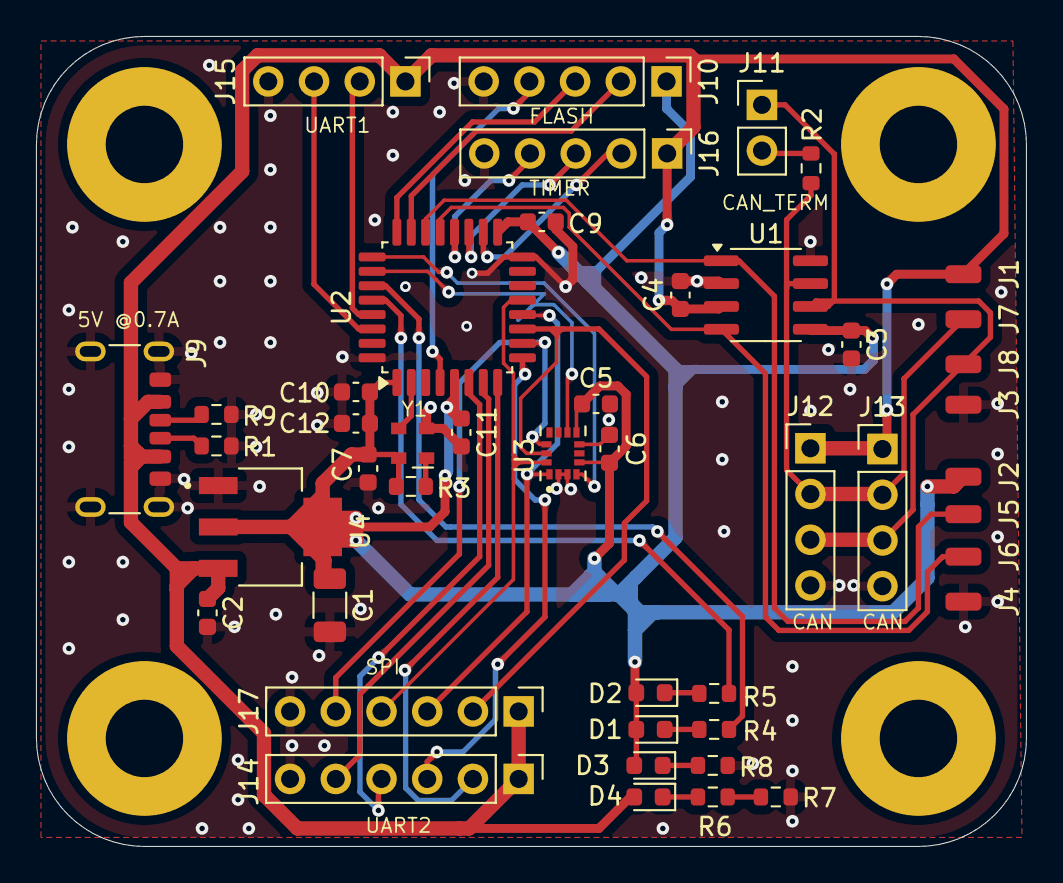
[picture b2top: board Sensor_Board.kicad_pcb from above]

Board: 4 copper layers, 55.0 x 45.0 mm, 50 parts (0 on the bottom side), 37 nets.

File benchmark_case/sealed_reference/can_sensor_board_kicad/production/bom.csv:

Designator,Footprint,Quantity,Value,LCSC Part #
C1,1206,1,100uF,"
C15008"
"C10, C11, C3, C4, C5, C6, C9",0603,7,100nF,C14663
C12,0603,1,1uF,"
C15849"
C2,0603,1,10uF,"
C19702"
C7,0603,1,10nF,C57112
"D1, D2, D3, D4",0603,4,LED,C5151486
"J1, J2, J3, J4, J5, J6, J7, J8",SolderWirePad_1x01_SMD_1x2mm,8,Conn_01x01,
"J10, J16",PinHeader_1x05_P2.54mm_Vertical,2,Conn_01x05,
J11,PinHeader_1x02_P2.54mm_Vertical,1,Conn_01x02,
"J12, J13, J15",PinHeader_1x04_P2.54mm_Vertical,3,Conn_01x04,
"J14, J17",PinHeader_1x06_P2.54mm_Vertical,2,Conn_01x06,
J9,USB_C_Receptacle_GCT_USB4125-xx-x-0190_6P_TopMnt_Horizontal,1,USB_C_Receptacle_PowerOnly_6P,C456012
"R1, R9",0603,2,5.1K,C23186
R2,0603,1,120R,"
C22787"
R3,0603,1,10k,C25804
"R4, R5, R6, R7, R8",0603,5,1k,C21190
U1,SOIC-8_3.9x4.9mm_P1.27mm,1,TJA1051T-3,"
C5342108"
U2,LQFP-32_7x7mm_P0.8mm,1,STM32F042K6Tx,C69216
U3,XDCR_ASM330LHHXTR,1,ASM330LHHXTR,C459826
U4,SOT230P700X180-4N,1,TLV1117-33,C37359
Y1,Oscillator_SMD_Abracon_ASDMB-4Pin_2.5x2.0mm,1,ASDDV-8.000MHZ-LR-T,C252325

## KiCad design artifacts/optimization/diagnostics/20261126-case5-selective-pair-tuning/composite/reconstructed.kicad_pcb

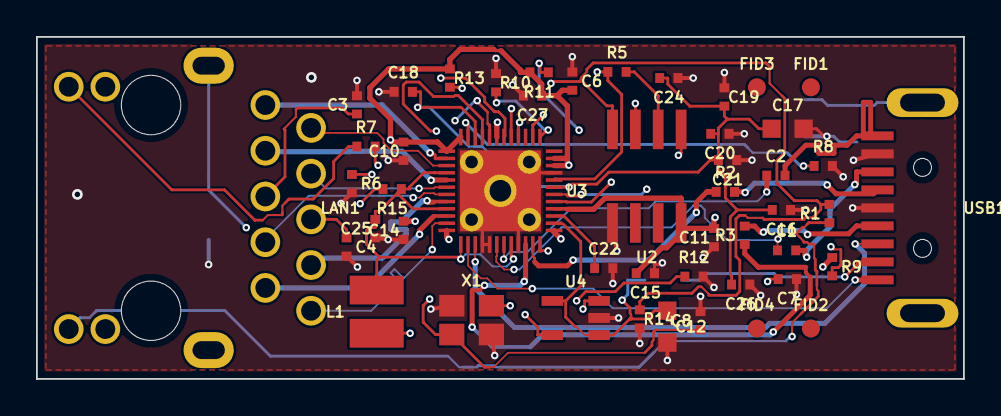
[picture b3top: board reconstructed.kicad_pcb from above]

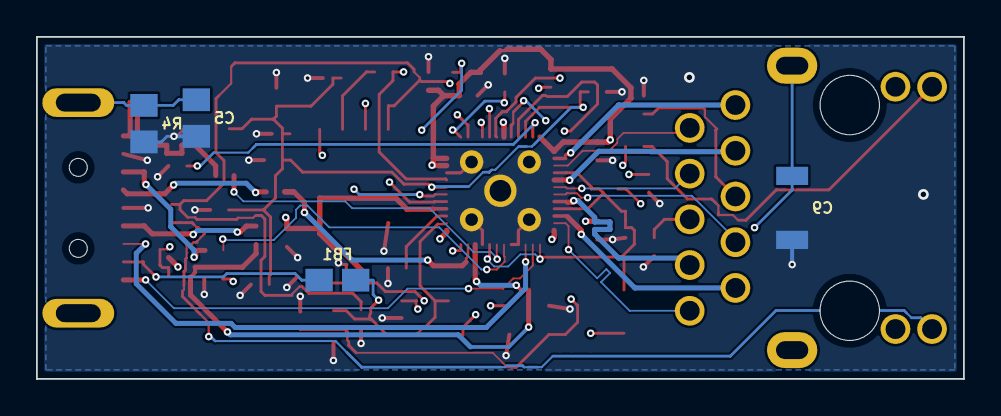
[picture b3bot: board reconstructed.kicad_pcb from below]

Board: 4 copper layers, 51.5 x 19.0 mm, 52 parts (4 on the bottom side), 43 nets.

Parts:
C1, C2, C3, C4, C10, C11, C14, C15, C16, C18, C19, C20, C21, C22, C24, C25, C26, C27: 100nF/10V/X5R /20%/0402; C_0402_5MIL_DWS
C5: 100nF/50V/Y5V/20%; C_0805_5MIL_DWS
C6: NA; C_0402_5MIL_DWS
C7, C8: 39pF/C0G/50VDC/0402; C_0402_5MIL_DWS
C9: 1nF/2000V/10%/X7R/1206; C_1206_5MIL_DWS_ISO
C12, C17: 2.2uF/X5R/6.3V/10%/0603; C_0603_5MIL_DWS
FB1: 600OHM/2A/UPZ2012E-601-2R0TF/0805; L_0805_5MIL_DWS
FID1, FID2: Fiducial; Fiducial1x3
FID3, FID4: Fiducial; Fiducial1x3_Paste
L1: 2.2uH/NRS3015T2R2MNGH; CD32
LAN1: TM211Q01FM22(LPJG16402AQNL); TM211Q01FM22
R1, R7: 1K/0402; R_0402_5MIL_DWS
R2, R3: 22R/0402; R_0402_5MIL_DWS
R4: 10R/0805; R_0805_5MIL_DWS
R5, R6, R10, R13, R14: NA; R_0402_5MIL_DWS
R8: 2.49K/1%/0402; R_0402_5MIL_DWS
R9, R11: 2.2K/0402; R_0402_5MIL_DWS
R12, R15: 1.1K/1%/0402; R_0402_5MIL_DWS
U2: NA(93LC46); SO-8
U3: RTL8153VC-CG; QFN48-6x6mm-OLIMEX_V2
U4: SY8089AAAC; SOT-23-5
USB1: USB1065; USB3_A_MALE
X1: 25MHz/20ppm/20pF/4P/3225; Oscillator-18.432MHz-3.2x2.5mm

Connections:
+3V3: C6.2, C10.2, C11.2, C14.2, C15.2, C27.1, LAN1.13, R9.1, R11.2, R13.1, U2.8 (VCC), U3.1 (AVDD33), U3.12 (AVDD33), U3.25 (AVDD33), U3.28 (DVDD33), U3.34 (VDDREG), U3.35 (VDDREG), U3.43 (DVDD33), U3.48 (AVDD33)
/LED0: LAN1.11, U3.30 (SPICSB/LED0)
/LED1: R5.1, R7.2, U3.32 (SPISCK/EESK/LED1)
/LED2: R1.2, R13.2, R14.1, U2.4 (DO), U3.41 (SPISDO/EEDO/LED2)
/M0_N: LAN1.2, U3.3 (MDI0_N)
/M0_P: LAN1.1, U3.2 (MDI0_P)
/M1_N: LAN1.4, U3.6 (MDI1_N)
/M1_P: LAN1.3, U3.5 (MDI1_P)
/M2_N: LAN1.8, U3.8 (MDI2_N)
/M2_P: LAN1.7, U3.7 (MDI2_P)
/M3_N: LAN1.10, U3.11 (MDI3_N)
/M3_P: LAN1.9, U3.10 (MDI3_P)
/U2D_N: R3.2, USB1.2 (USBDN)
/U2D_P: R2.2, USB1.3 (USBDP)
/U2_N: R3.1, U3.22 (U2D_N)
/U2_P: R2.1, U3.23 (U2D_P)
/U3SRX_N: U3.15 (U3SSRX_N), USB1.8 (SSRXN)
/U3SRX_P: U3.14 (U3SSRX_P), USB1.9 (SSRXP)
/U3STX_N: C2.2, USB1.5 (SSTXN)
/U3STX_P: C1.2, USB1.6 (SSTXP)
/U3TX_N: C2.1, U3.19 (U3SSTX_N)
/U3TX_P: C1.1, U3.18 (U3SSTX_P)
/V12: C16.2, C17.1, C18.2, C19.2, C20.2, C21.2, C24.2, C25.2, C26.2, L1.2, R15.1, U3.4 (AVDD10), U3.9 (AVDD10), U3.13 (U3VDD10), U3.20 (U3VDD10), U3.24 (U2VDD10), U3.31 (DVDD10), U3.42 (DVDD10), U3.46 (AVDD10)
/VBUS: FB1.1, USB1.1 (VBUS)
GND: C3.2, C4.2, C5.2, C6.1, C7.1, C8.2, C9.2, C10.1, C11.1, C12.2, C14.1, C15.1, C16.1, C17.2, C18.1, C19.1, C20.1, C21.1, C22.2, C24.1, C25.1, C26.1, C27.2, R4.2, R6.2, R8.2, R10.1, R12.2, R14.2, U2.5 (VSS), U3.16 (U3GND), U3.17 (U3GND), U3.21 (U2GND), U3.33 (ENSWREG), U3.49 (GND(EP)), U4.2 (GND), USB1.4 (GNDP), USB1.7 (GNDD), X1.2, X1.4
unnamed: C5.1, R4.1, USB1.0
unnamed: C9.1, LAN1.SH1, LAN1.SH2
unnamed: C3.1, LAN1.5
unnamed: C4.1, LAN1.6
unnamed: LAN1.12, R7.1
unnamed: LAN1.14, R1.1
unnamed: R5.2, U2.2 (CLK)
unnamed: U2.1 (CS), U3.40 (EECS/SCL)
unnamed: R6.1, U2.3 (DI), U3.38 (SPISDI/SDA/EEDI)
unnamed: C7.2, U3.44 (CKXTAL1), X1.3
unnamed: C8.1, U3.45 (CKXTAL2), X1.1
unnamed: C22.1, U3.27 (DVDD10_UPS)
unnamed: R11.1, U3.29 (GPIO)
unnamed: R8.1, U3.47 (RSET)
unnamed: C12.1, FB1.2, U3.26 (VDD5), U4.1 (EN), U4.4 (IN)
unnamed: R9.2, R10.2, U3.37 (XTALDET)
unnamed: R12.1, R15.2, U4.5 (FB)
unnamed: L1.1, U4.3 (LX)
